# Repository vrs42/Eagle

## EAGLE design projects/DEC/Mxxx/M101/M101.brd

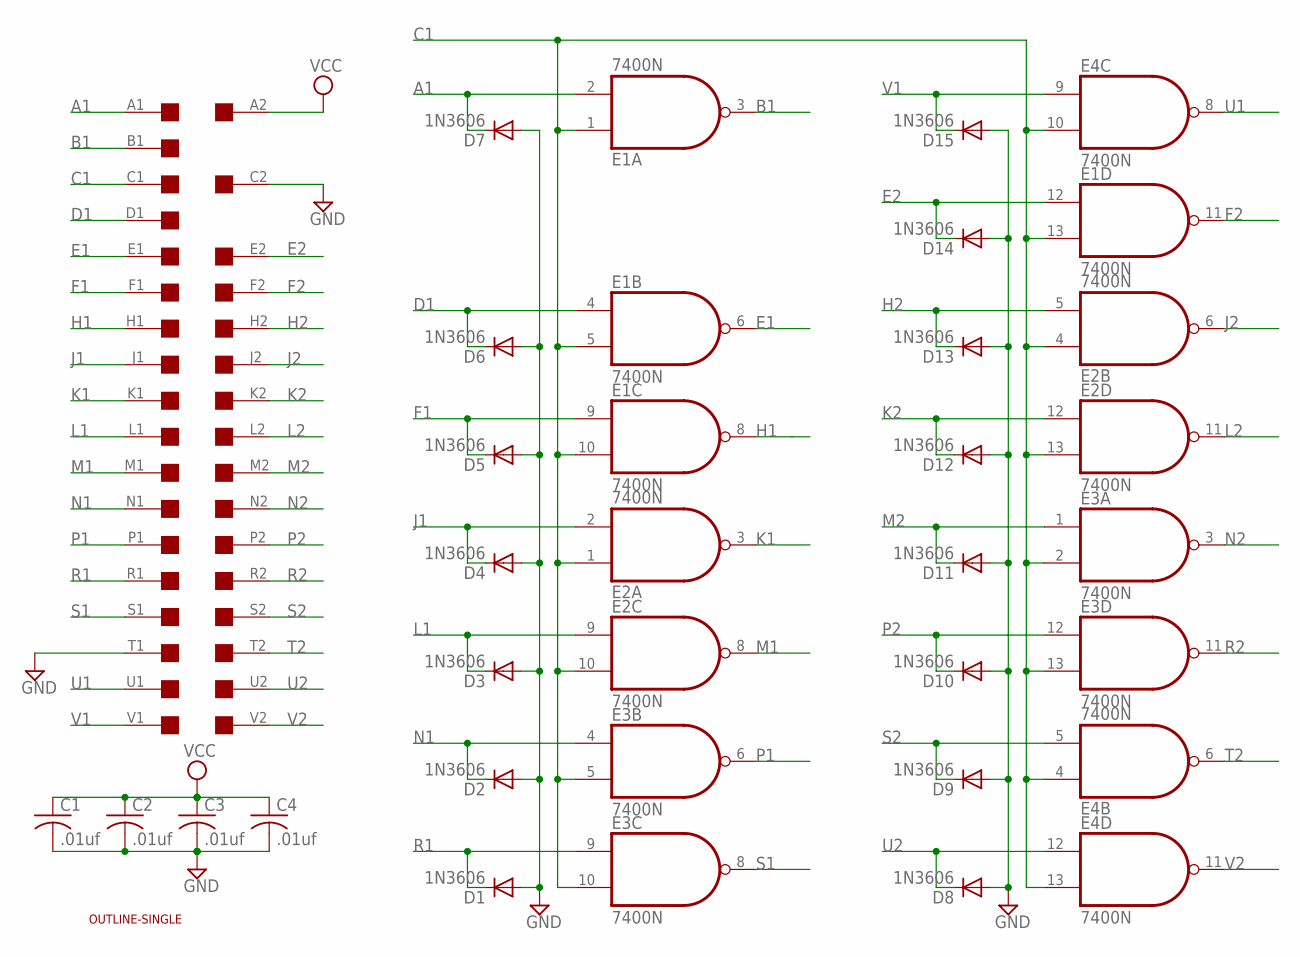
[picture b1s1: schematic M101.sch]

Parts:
C1, C2, C3, C4: .01uf; C050-025X075
D1, D2, D3, D4, D5, D6, D7, D8, D9, D10, D11, D12, D13, D14, D15: 1N3606; DO35-10
E1, E2, E3, E4: 7400N; DIL14
U$1: SINGLE; EDGE-CON2
U$4: OUTLINE-SINGLE; SINGLE

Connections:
A1: D7.C, E1.2 (I1), U$1.A1
B1: E1.3 (O), U$1.B1
C1: E1.1 (I0), E1.5 (I1), E1.10 (I1), E1.13 (I1), E2.1 (I0), E2.4 (I0), E2.10 (I1), E2.13 (I1), E3.2 (I1), E3.5 (I1), E3.10 (I1), E3.13 (I1), E4.4 (I0), E4.10 (I1), E4.13 (I1), U$1.C1
D1: D6.C, E1.4 (I0), U$1.D1
E1: E1.6 (O), U$1.E1
E2: D14.C, E1.12 (I0), U$1.E2
F1: D5.C, E1.9 (I0), U$1.F1
F2: E1.11 (O), U$1.F2
GND: C1.2, C2.2, C3.2, C4.2, D1.A, D2.A, D3.A, D4.A, D5.A, D6.A, D7.A, D8.A, D9.A, D10.A, D11.A, D12.A, D13.A, D14.A, D15.A, E1.7 (GND), E2.7 (GND), E3.7 (GND), E4.7 (GND), U$1.C2, U$1.T1
H1: E1.8 (O), U$1.H1
H2: D13.C, E2.5 (I1), U$1.H2
J1: D4.C, E2.2 (I1), U$1.J1
J2: E2.6 (O), U$1.J2
K1: E2.3 (O), U$1.K1
K2: D12.C, E2.12 (I0), U$1.K2
L1: D3.C, E2.9 (I0), U$1.L1
L2: E2.11 (O), U$1.L2
M1: E2.8 (O), U$1.M1
M2: D11.C, E3.1 (I0), U$1.M2
N1: D2.C, E3.4 (I0), U$1.N1
N2: E3.3 (O), U$1.N2
P1: E3.6 (O), U$1.P1
P2: D10.C, E3.12 (I0), U$1.P2
R1: D1.C, E3.9 (I0), U$1.R1
R2: E3.11 (O), U$1.R2
S1: E3.8 (O), U$1.S1
S2: D9.C, E4.5 (I1), U$1.S2
T2: E4.6 (O), U$1.T2
U1: E4.8 (O), U$1.U1
U2: D8.C, E4.12 (I0), U$1.U2
V1: D15.C, E4.9 (I0), U$1.V1
V2: E4.11 (O), U$1.V2
VCC: C1.1, C2.1, C3.1, C4.1, E1.14 (VCC), E2.14 (VCC), E3.14 (VCC), E4.14 (VCC), U$1.A2

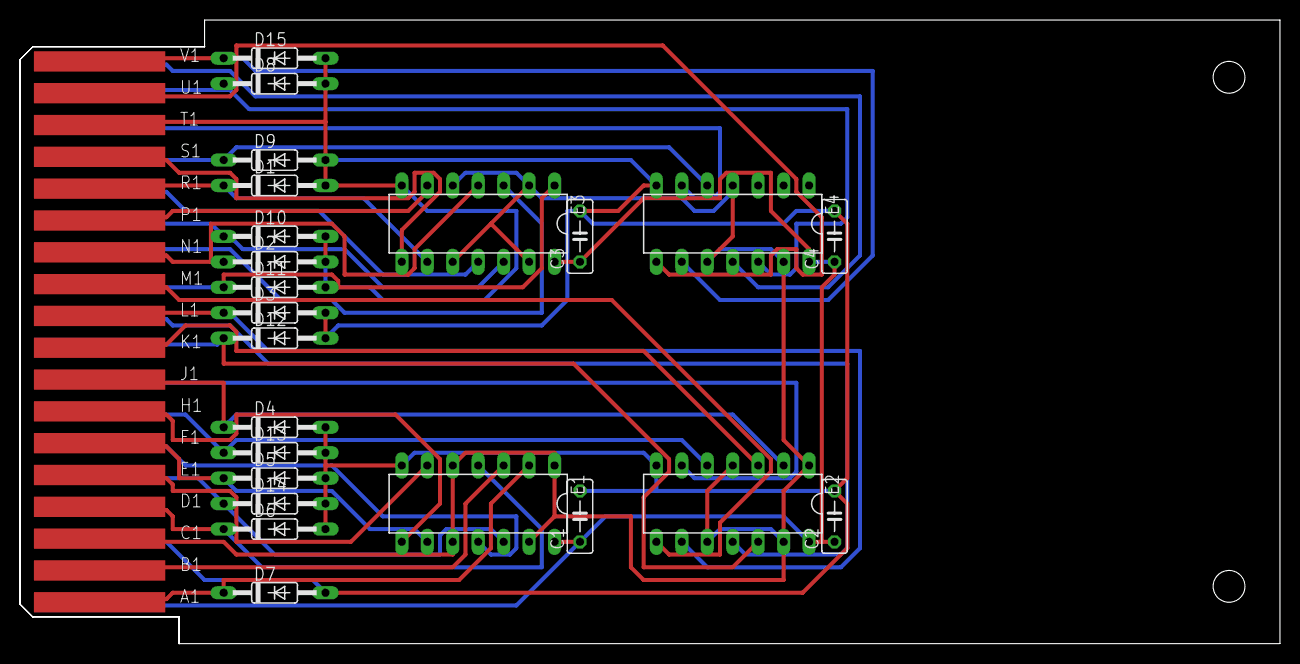
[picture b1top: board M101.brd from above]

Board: 2 copper layers, 125.7 x 62.2 mm, 25 parts (0 on the bottom side), 33 nets.

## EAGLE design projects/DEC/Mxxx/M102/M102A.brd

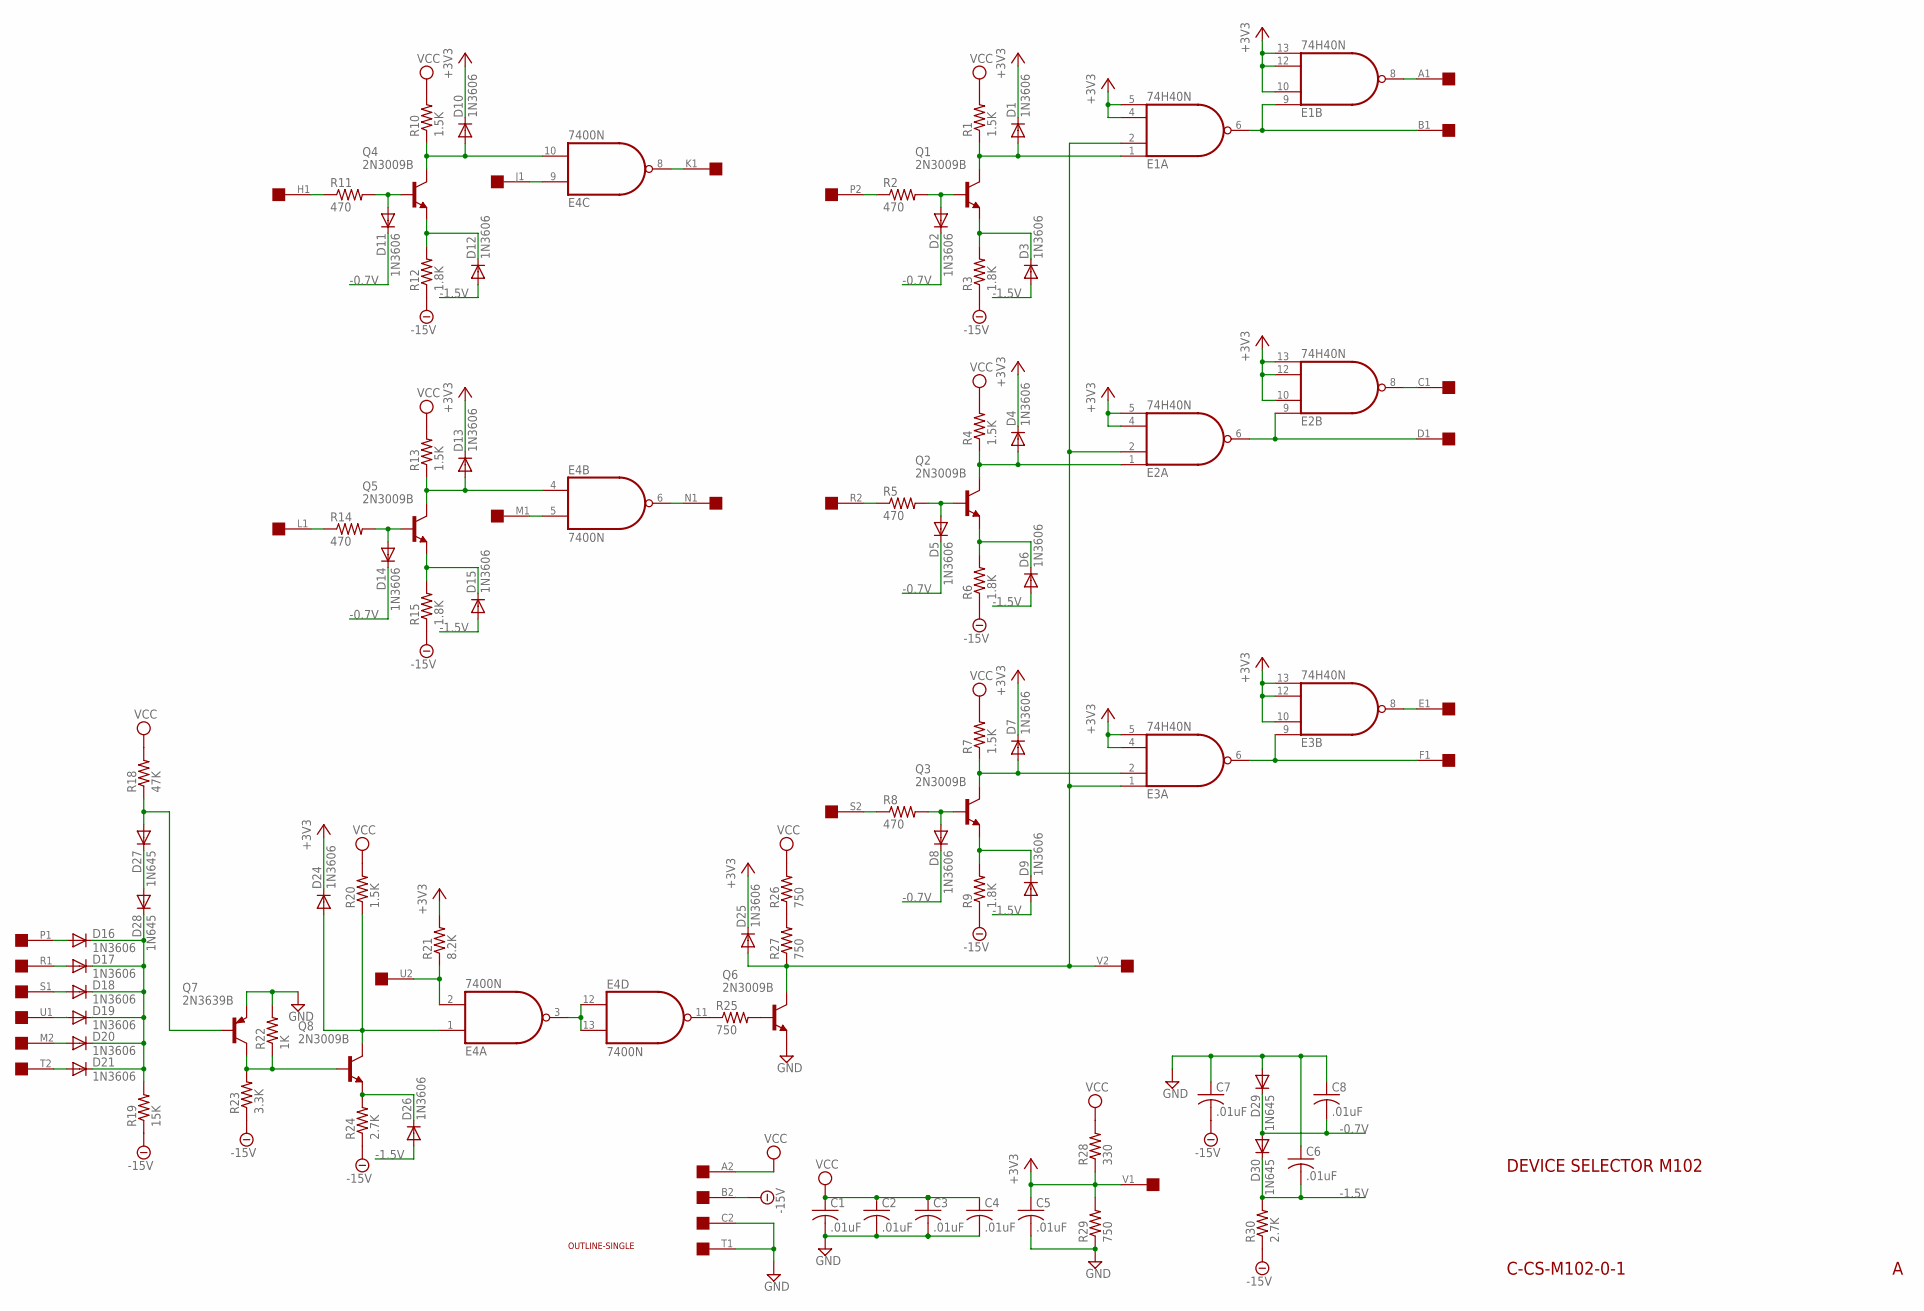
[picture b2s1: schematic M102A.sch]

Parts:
C1, C2, C3, C4, C5, C6, C7, C8: .01uF; C050-025X075
D1, D2, D3, D4, D5, D6, D7, D8, D9, D10, D11, D12, D13, D14, D15, D16, D17, D18, D19, D20, D21, D24, D25, D26: 1N3606; DO35-10
D27, D28, D29, D30: 1N645; DO35-10
E1, E2, E3: 74H40N; DIL14
E4: 7400N; DIL14
Q1, Q2, Q3, Q4, Q5, Q6, Q8: 2N3009B; TO39
Q7: 2N3639B; TO39
R1, R4, R7, R10, R13, R20: 1.5K; 0207/10
R2, R5, R8, R11, R14: 470; 0207/10
R3, R6, R9, R12, R15: 1.8K; 0207/10
R18: 47K; 0207/10
R19: 15K; 0207/10
R21: 8.2K; 0207/10
R22: 1K; 0207/10
R23: 3.3K; 0207/10
R24, R30: 2.7K; 0207/10
R25, R26, R27, R29: 750; 0207/10
R28: 330; 0207/10
U$8: SINGLE; EDGE-CON2
U$9: OUTLINE-SINGLE; SINGLE

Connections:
+3V3: C5.1, D1.C, D4.C, D7.C, D10.C, D13.C, D24.C, D25.C, E1.4 (I2), E1.5 (I3), E1.10 (I1), E1.12 (I2), E1.13 (I3), E2.4 (I2), E2.5 (I3), E2.10 (I1), E2.12 (I2), E2.13 (I3), E3.4 (I2), E3.5 (I3), E3.10 (I1), E3.12 (I2), E3.13 (I3), R21.2, R28.1, R29.2, U$8.V1
-0.7V: C8.2, D2.C, D5.C, D8.C, D11.C, D14.C, D29.C, D30.A
-1.5V: C6.2, D3.A, D6.A, D9.A, D12.A, D15.A, D26.A, D30.C, R30.2
-15V: C7.2, R3.1, R6.1, R9.1, R12.1, R15.1, R19.1, R23.1, R24.1, R30.1, U$8.B2
A1: E1.8 (O), U$8.A1
B1: E1.6 (O), E1.9 (I0), U$8.B1
C1: E2.8 (O), U$8.C1
D1: E2.6 (O), E2.9 (I0), U$8.D1
E1: E3.8 (O), U$8.E1
F1: E3.6 (O), E3.9 (I0), U$8.F1
GND: C1.2, C2.2, C3.2, C4.2, C5.2, C6.1, C7.1, C8.1, D29.A, E1.7 (GND), E2.7 (GND), E3.7 (GND), E4.7 (GND), Q6.1 (E), Q7.1 (E), R22.2, R29.1, U$8.C2, U$8.T1
H1: R11.1, U$8.H1
J1: E4.9 (I0), U$8.J1
K1: E4.8 (O), U$8.K1
L1: R14.1, U$8.L1
M1: E4.5 (I1), U$8.M1
M2: D20.A, U$8.M2
N1: E4.6 (O), U$8.N1
unnamed: D27.A, Q7.2 (B), R18.1
unnamed: E4.11 (O), R25.1
unnamed: Q6.2 (B), R25.2
unnamed: D27.C, D28.A
unnamed: R26.1, R27.2
unnamed: Q7.3 (C), Q8.2 (B), R22.1, R23.2
unnamed: D26.C, Q8.1 (E), R24.2
unnamed: D24.A, E4.1 (I0), Q8.3 (C), R20.1
unnamed: E4.3 (O), E4.12 (I0), E4.13 (I1)
unnamed: D10.A, E4.10 (I1), Q4.3 (C), R10.1
unnamed: D11.A, Q4.2 (B), R11.2
unnamed: D16.C, D17.C, D18.C, D19.C, D20.C, D21.C, D28.C, R19.2
unnamed: D1.A, E1.1 (I0), Q1.3 (C), R1.1
unnamed: D12.C, Q4.1 (E), R12.2
unnamed: D13.A, E4.4 (I0), Q5.3 (C), R13.1
unnamed: D14.A, Q5.2 (B), R14.2
unnamed: D2.A, Q1.2 (B), R2.2
unnamed: D15.C, Q5.1 (E), R15.2
unnamed: D3.C, Q1.1 (E), R3.2
unnamed: D4.A, E2.1 (I0), Q2.3 (C), R4.1
unnamed: D5.A, Q2.2 (B), R5.2
unnamed: D6.C, Q2.1 (E), R6.2
unnamed: D7.A, E3.2 (I1), Q3.3 (C), R7.1
unnamed: D8.A, Q3.2 (B), R8.2
unnamed: D9.C, Q3.1 (E), R9.2
P1: D16.A, U$8.P1
P2: R2.1, U$8.P2
R1: D17.A, U$8.R1
R2: R5.1, U$8.R2
S1: D18.A, U$8.S1
S2: R8.1, U$8.S2
T2: D21.A, U$8.T2
U1: D19.A, U$8.U1
U2: E4.2 (I1), R21.1, U$8.U2
V2: D25.A, E1.2 (I1), E2.2 (I1), E3.1 (I0), Q6.3 (C), R27.1, U$8.V2
VCC: C1.1, C2.1, C3.1, C4.1, E1.14 (VCC), E2.14 (VCC), E3.14 (VCC), E4.14 (VCC), R1.2, R4.2, R7.2, R10.2, R13.2, R18.2, R20.2, R26.2, R28.2, U$8.A2

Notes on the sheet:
DEVICE SELECTOR M102
C-CS-M102-0-1

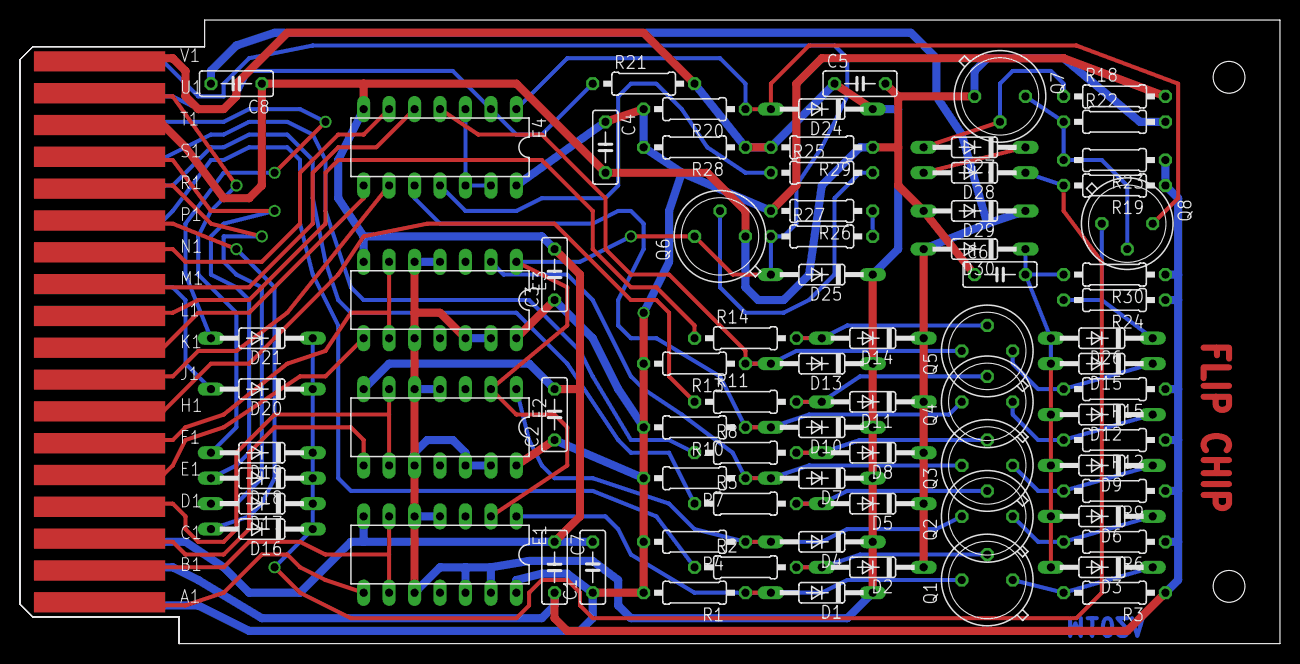
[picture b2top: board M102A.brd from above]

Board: 2 copper layers, 125.7 x 62.2 mm, 78 parts (0 on the bottom side), 54 nets.

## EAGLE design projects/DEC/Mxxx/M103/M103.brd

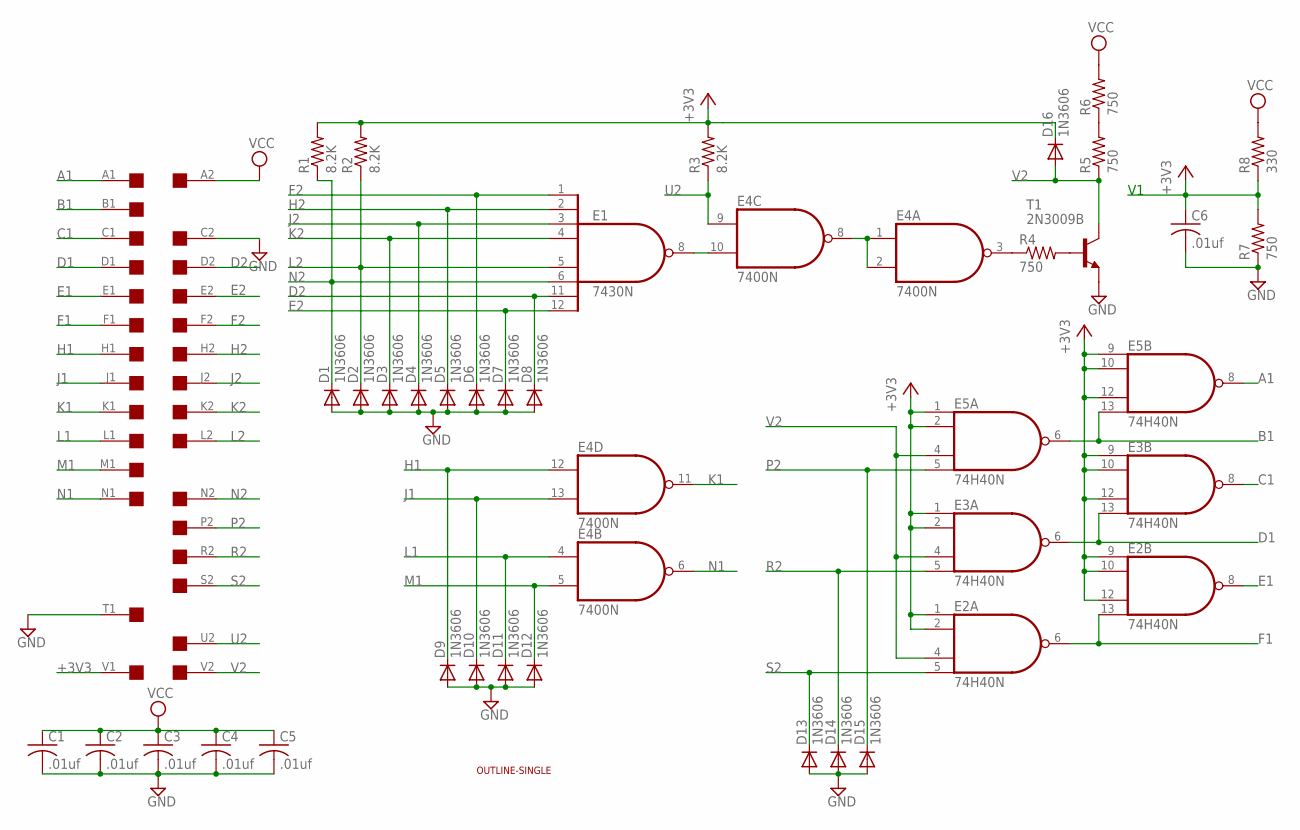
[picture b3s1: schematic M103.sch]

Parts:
C1, C2, C3, C4, C5, C6: .01uf; C050-025X075
D1, D2, D3, D4, D5, D6, D7, D8, D9, D10, D11, D12, D13, D14, D15, D16: 1N3606; DO35-10
E1: 7430N; DIL14
E2, E3, E5: 74H40N; DIL14
E4: 7400N; DIL14
R1, R2, R3: 8.2K; 0207/10
R4, R5, R6, R7: 750; 0207/10
R8: 330; 0207/10
T1: 2N3009B; TO39
U$8: SINGLE; EDGE-CON2
U$9: OUTLINE-SINGLE; SINGLE

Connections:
+3V3: C6.1, D16.C, E2.1 (I0), E2.2 (I1), E2.9 (I0), E2.10 (I1), E2.12 (I2), E3.1 (I0), E3.2 (I1), E3.9 (I0), E3.10 (I1), E3.12 (I2), E5.1 (I0), E5.2 (I1), E5.9 (I0), E5.10 (I1), E5.12 (I2), R1.2, R2.2, R3.2, R7.2, R8.1, U$8.V1
A1: E5.8 (O), U$8.A1
B1: E5.6 (O), E5.13 (I3), U$8.B1
C1: E3.8 (O), U$8.C1
D1: E3.6 (O), E3.13 (I3), U$8.D1
D2: D8.C, E1.11 (I6), U$8.D2
E1: E2.8 (O), U$8.E1
E2: D7.C, E1.12 (I7), U$8.E2
F1: E2.6 (O), E2.13 (I3), U$8.F1
F2: D6.C, E1.1 (I0), U$8.F2
GND: C1.2, C2.2, C3.2, C4.2, C5.2, C6.2, D1.A, D2.A, D3.A, D4.A, D5.A, D6.A, D7.A, D8.A, D9.A, D10.A, D11.A, D12.A, D13.A, D14.A, D15.A, E1.7 (GND), E2.7 (GND), E3.7 (GND), E4.7 (GND), E5.7 (GND), R7.1, T1.1 (E), U$8.C2, U$8.T1
H1: D9.C, E4.12 (I0), U$8.H1
H2: D5.C, E1.2 (I1), U$8.H2
J1: D10.C, E4.13 (I1), U$8.J1
J2: D4.C, E1.3 (I2), U$8.J2
K1: E4.11 (O), U$8.K1
K2: D3.C, E1.4 (I3), U$8.K2
L1: D11.C, E4.4 (I0), U$8.L1
L2: D2.C, E1.5 (I4), R2.1, U$8.L2
M1: D12.C, E4.5 (I1), U$8.M1
N1: E4.6 (O), U$8.N1
N2: D1.C, E1.6 (I5), R1.1, U$8.N2
unnamed: E4.3 (O), R4.1
unnamed: R4.2, T1.2 (B)
unnamed: R5.2, R6.1
unnamed: E1.8 (O), E4.10 (I1)
unnamed: E4.1 (I0), E4.2 (I1), E4.8 (O)
P2: D15.C, E5.5 (I3), U$8.P2
R2: D14.C, E3.5 (I3), U$8.R2
S2: D13.C, E2.5 (I3), U$8.S2
U2: E4.9 (I0), R3.1, U$8.U2
V2: D16.A, E2.4 (I2), E3.4 (I2), E5.4 (I2), R5.1, T1.3 (C), U$8.V2
VCC: C1.1, C2.1, C3.1, C4.1, C5.1, E1.14 (VCC), E2.14 (VCC), E3.14 (VCC), E4.14 (VCC), E5.14 (VCC), R6.2, R8.2, U$8.A2

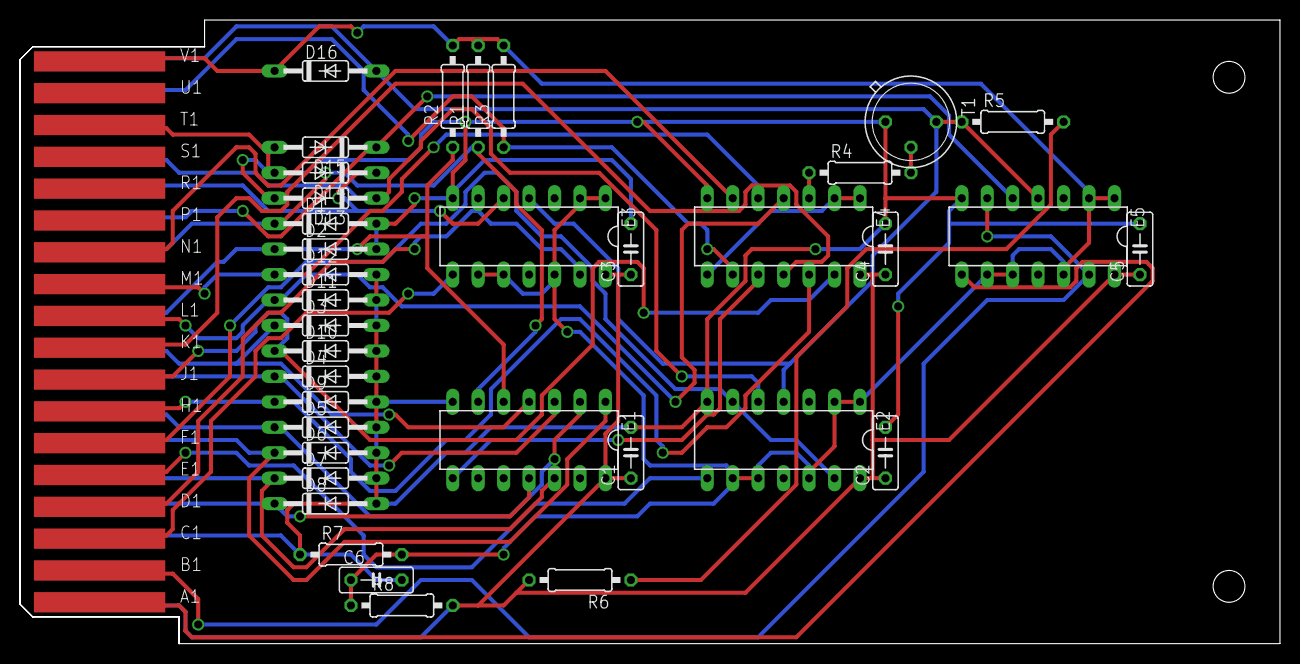
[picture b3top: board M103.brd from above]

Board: 2 copper layers, 125.7 x 62.2 mm, 38 parts (0 on the bottom side), 33 nets.
